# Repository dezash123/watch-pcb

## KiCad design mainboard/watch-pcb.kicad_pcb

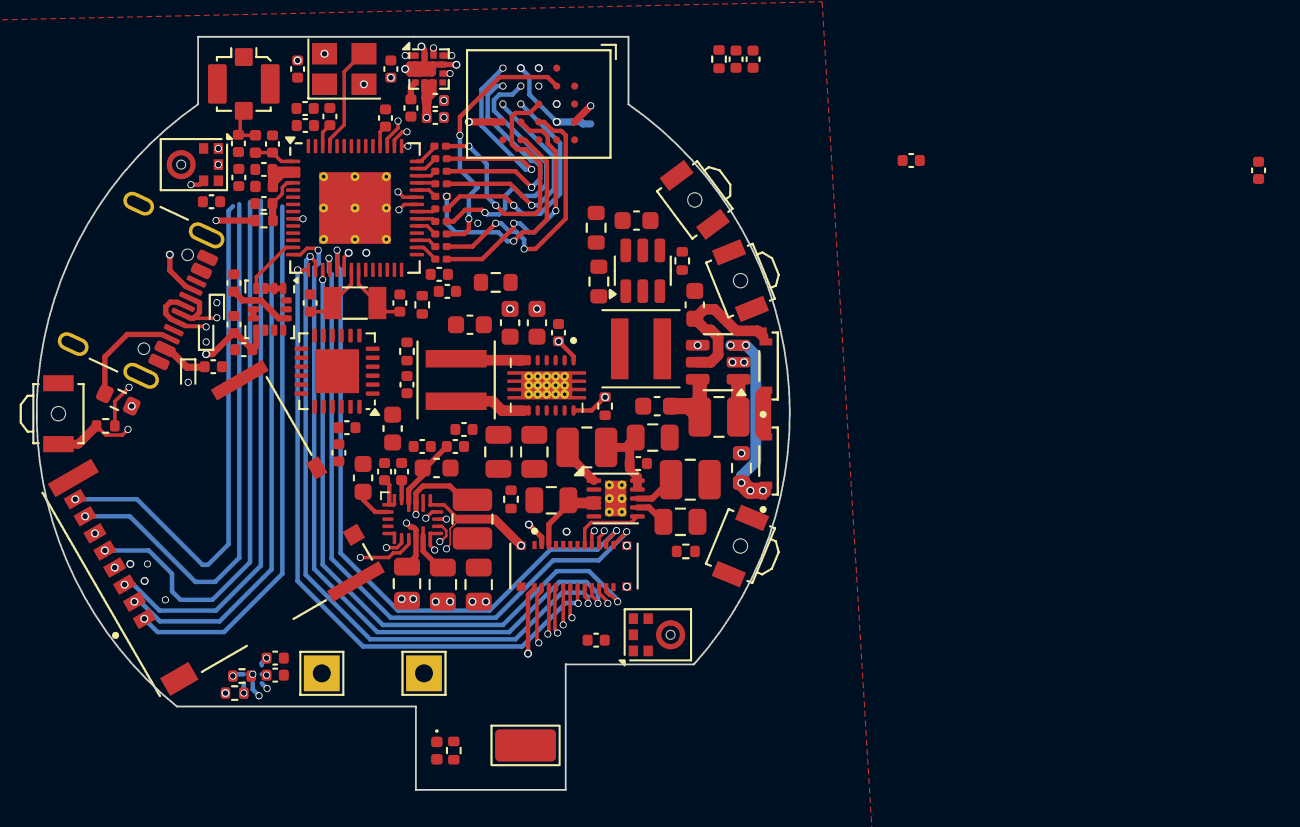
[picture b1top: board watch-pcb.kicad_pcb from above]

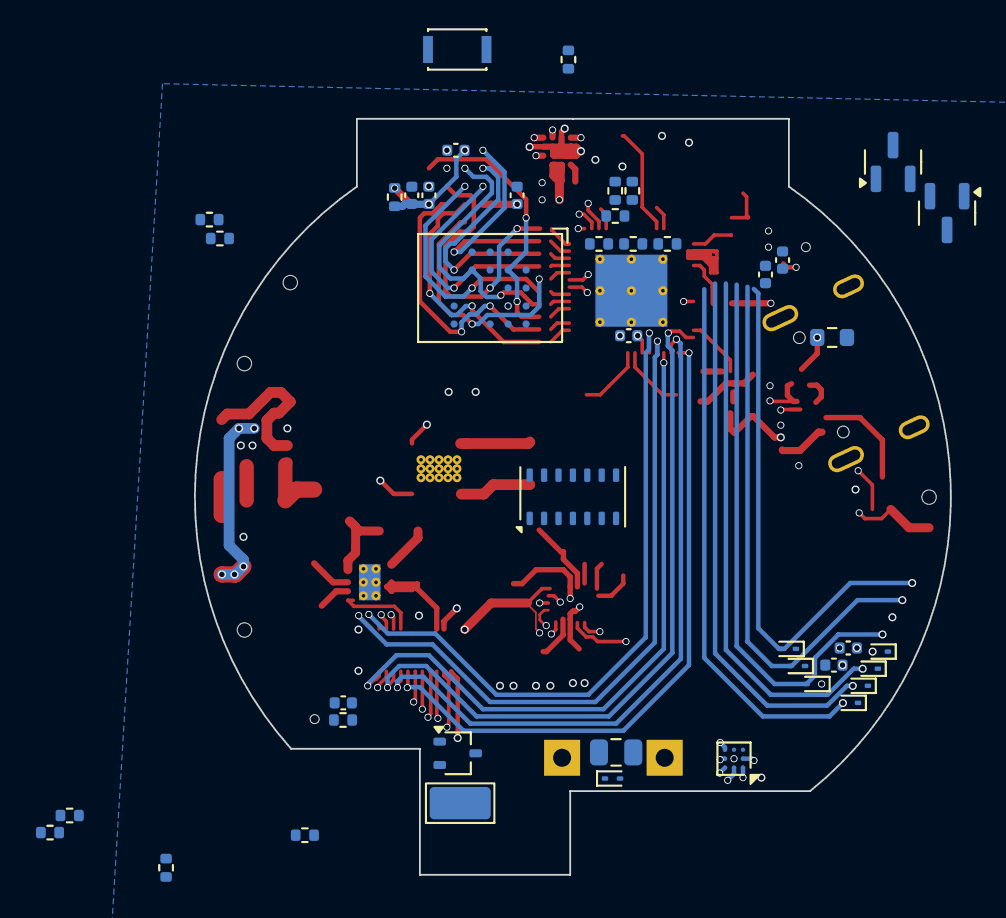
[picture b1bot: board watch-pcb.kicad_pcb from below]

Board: 6 copper layers, 42.0 x 42.0 mm, 166 parts (43 on the bottom side), 111 nets.

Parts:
C1, C4, C9, C17, C19, C23, C27, C41, C44, C48, C70, C72: 1uF; C_0402_1005Metric
C2, C10, C11, C13, C14, C16, C24, C25, C26, C28, C29, C30, C35, C45, C50, C56, C59, C61, C67, C68, C69, C74, C76, C77: 100nF; C_0402_1005Metric
C3: 10uF; C_0603_1608Metric
C5: 47nF; C_0402_1005Metric
C6, C7, C8: 22uF; C_0603_1608Metric
C12, C73, C81: 4.7uF; C_0603_1608Metric
C15, C55, C57, C58, C64, C65, C79, C80: 10uF; C_0805_2012Metric
C18, C33: 10nF; C_0402_1005Metric
C20: 2.2uF; C_0402_1005Metric
C21, C22: 1.5pF; C_0402_1005Metric
C31, C32, C46, C47: C; C_0402_1005Metric
C34, C60: 10uF; C_0402_1005Metric
C51: 1uF; C_0603_1608Metric
C63: 22uF; C_0805_2012Metric
C82: 220nF; C_0603_1608Metric
D1, D2: CUW Y3SH.B2-JD-42-6T; LED_CUW_Y3SH.B2-GFJD-5J6T-Z242-20-R18-Z
D3, D6, D7, D8: ESD9B5.0ST5G; D_SOD-923
D4: CHARGING; LED_0402_1005Metric
D9, D10, D11, D12, D13, D14, D15: ESD9B3.3ST5G; D_SOD-923
J2: USB_C_Receptacle; USB_C_Receptacle_GCT_USB4105-xx-A_16P_TopMnt_Horizontal
J3: ESP_ANT; U.FL_Molex_MCRF_73412-0110_Vertical
J5: Micro_SD_Card; MOLEX_503398-1892
J6: TT143AMC12C; MOLEX_505550-2420
J7: BATT+; TestPoint_THTPad_2.0x2.0mm_Drill1.0mm
J8: BATT-; TestPoint_THTPad_2.0x2.0mm_Drill1.0mm
J9: LASER+; TestPoint_Keystone_5015_Micro_Mini
J10: LASER-; TestPoint_Keystone_5015_Micro_Mini
L1: XFL4020-152ME; L_Coilcraft_XxL4040
L2: CIGT252010EH1R0MNE; L_1008_2520Metric
L3: XFL4020-222ME; L_Coilcraft_XxL4040
L4: 2.7nH; L_0402_1005Metric
L5: LQG15HN2N0C02D; L_0402_1005Metric
L6: 24nH; C_0402_1005Metric
L7, L8: 10uH; L_1008_2520Metric
L9: LQM2HPN4R7MG0L; L_1008_2520Metric
MK1, MK2: ICS-43434; InvenSense_ICS-43434-6_3.5x2.65mm
Q1: BSS214NW; SOT-323_SC-70
Q2, Q3: BSS138; SOT-23
R1, R18, R23, R24, R38, R39, R40, R41, R42, R43: 10k; R_0402_1005Metric
R4: 5; R_0603_1608Metric
R8, R35, R37, R44, R50, R51, R52, R53, R54, R55: 0; R_0201_0603Metric
R9: 5k; R_0402_1005Metric
R10: 1M; R_0402_1005Metric
R11: 5.32k; R_0402_1005Metric
R12: 30.1; R_0402_1005Metric
R13: R; R_0402_1005Metric
R14, R15, R17, R19, R20, R45, R46, R47, R48, R49: 100k; R_0402_1005Metric
R16, R22: 5.1k; R_0603_1608Metric
R26: 0; R_0402_1005Metric
R28: 200k; R_0603_1608Metric
R29: 100k; R_0603_1608Metric
R30: 499k; R_0402_1005Metric
R36: 1k; C_0402_1005Metric
SW1, SW2, SW3, SW4: B3U-3000P-B; SW_SPST_B3U-3000P-B
SW8: BOOT; SW_SPST_CK_KXT3
TH1: 103AT-2 10k; R_0603_1608Metric
U1: TPS63021; Texas_VSON-14_3x4mm_ThermalPad
U2: BQ25628E; Texas_WQFN-18_2.5x3.0mm_P0.4mm
U4: BQ27427YZFR; Texas_DSBGA-9_1.62x1.58mm_Layout3x3_P0.5mm
U5: MX25UM51245GXDI00; BGA-24_6.0x8.0mm_Layout5x5_P1.0mm
U6: S80KS5123GABHV020; BGA-24_6.0x8.0mm_Layout5x5_P1.0mm
U8: TCA9535MRGER; VQFN-24-1EP_4x4mm_P0.5mm_EP2.45x2.45mm
U9: TPS65631W; WSON-10-1EP_2.5x2.5mm_P0.5mm_EP1.2x2mm_ThermalVias
U10: LIS3MDL; LGA-12_2x2mm_P0.5mm
U11: ESP32-S3; QFN-56-1EP_7x7mm_P0.4mm_EP4x4mm_ThermalVias
U12: LSM6DSOXTR; LGA-14_3x2.5mm_P0.5mm_LayoutBorder3x4y
U14: MAX30102; Maxim_OLGA-14_3.3x5.6mm_P0.8mm
U16: AP3019AK; SOT-23-6
U17: TLV62569DDC; SOT-23-6
Y1: 32.768kHz; Crystal_SMD_3215-2Pin_3.2x1.5mm
Y2: 40MHz(10ppm); Crystal_SMD_3225-4Pin_3.2x2.5mm

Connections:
+1V8: C9.1, C10.1, C23.1, C24.2, C25.1, C26.1, C27.1, C28.1, C29.1, C30.1, C72.2, C76.2, L3.2, R19.1, R20.1, R28.1, U5.B4 (VCC), U5.D1 (VCCQ), U5.E4 (VCCQ), U6.B4 (VCC), U6.D1 (VCCQ), U6.E4 (VCCQ), U11.29 (VDD_SPI), U14.11 (VDD)
+3V3: C4.1, C6.2, C7.2, C8.2, C11.1, C13.1, C16.1, C17.1, C33.1, C34.1, C44.2, C45.1, C48.2, C50.2, C55.2, C56.1, C60.2, C61.2, C67.2, C68.2, C69.2, C70.2, C73.1, C74.1, C77.1, D15.2 (A2), J5.4 (VDD), J6.1 (VDD), J6.19 (IOVCC), J6.20 (VDD), J9.1, L5.2, L7.1, MK1.5 (VDD), MK2.2 (LR), MK2.5 (VDD), R10.1, R13.2, R15.2, R17.2, R24.2, R38.1, R39.1, R40.1, R41.1, R42.1, R43.1, R46.1, R47.1, R48.1, R49.1, SW8.1, U1.3 (FB), U1.4 (VOUT), U1.5 (VOUT), U8.21 (VCC), U9.9 (AVIN), U9.10 (PVIN), U10.5 (Vdd), U10.6 (Vdd_IO), U10.10 (~CS), U11.20 (VDD3P3_RTC), U11.46 (VDD3P3_CPU), U11.55 (VDDA), U11.56 (VDDA), U12.5 (VDDIO), U12.8 (VDD), U12.12 (CS), U14.9 (VLED+), U14.10 (VLED+)
+BATT: C15.2, C19.2, C63.1, D3.2 (A2), J7.1, U2.8 (BAT), U4.C3 (BAT)
+VSW: C2.2, C51.1, C64.1, C65.1, C79.1, C80.1, C81.1, L2.2, L9.2, R30.2, U1.1 (VINA), U1.10 (VIN), U1.11 (VIN), U2.9 (SYS), U4.C2 (SRX), U16.6 (V_{IN}), U17.1 (EN), U17.4 (VIN)
/ESP MCU/BOOT: Q2.1 (G), Q3.1 (G), R1.2, SW8.2
/ESP MCU/CLK_N: C47.2, U11.53 (XTAL_N), Y2.3
/ESP MCU/CLK_P: L6.2, U11.54 (XTAL_P)
/ESP MCU/EN: R10.2, R23.1, U1.14 (PG)
/ESP MCU/ESP_ANT: C22.1, L4.2, U11.1 (LNA_IN)
/ESP MCU/EXT_INT: R24.1, U8.22 (~INT), U11.27 (GPIO21)
/ESP MCU/EXT_IO1: J6.5 (RST), U8.1 (P00)
/ESP MCU/EXT_IO2: J6.15 (RST), U8.2 (P01)
/ESP MCU/EXT_IO3: R47.2, SW2.1, U8.3 (P02)
/ESP MCU/EXT_IO4: R48.2, SW3.2, U8.4 (P03)
/ESP MCU/EXT_IO5: R49.2, SW4.1, U8.5 (P04)
/ESP MCU/EXT_IO6: U8.6 (P05), U10.7 (INT)
/ESP MCU/EXT_IO7: R17.1, U4.A1 (GPOUT), U8.7 (P06)
/ESP MCU/EXT_IO8: R15.1, U2.11 (INT), U8.8 (P07)
/ESP MCU/EXT_IO9: R14.1, U1.13 (PS/SYNC), U8.10
/ESP MCU/FSPI_CLK: J6.11 (SCL), U11.17 (GPIO12)
/ESP MCU/FSPI_CS: J6.7 (CS), U11.15 (GPIO10)
/ESP MCU/FSPI_D: J6.8 (D0), U11.16 (GPIO11)
/ESP MCU/FSPI_HD: J6.9 (D3), U11.14 (GPIO9)
/ESP MCU/FSPI_Q: J6.13 (D1), U11.18 (GPIO13)
/ESP MCU/FSPI_WP: J6.14 (D2), U11.19 (GPIO14)
/ESP MCU/I2S_SCK: MK1.4 (SCK), MK2.4 (SCK), U11.45 (MTDO)
/ESP MCU/I2S_SD: MK1.6 (SD), MK2.6 (SD), R45.2, U11.43 (GPIO38)
/ESP MCU/I2S_WS: MK1.1 (WS), MK2.1 (WS), U11.44 (MTCK)
/ESP MCU/IO1: R26.2, U11.9 (GPIO4)
/ESP MCU/IO2: J6.2 (INT), U11.10 (GPIO5)
/ESP MCU/IO3: J6.16 (TE), U11.11 (GPIO6)
/ESP MCU/IO4: R46.2, U11.12 (GPIO7), U14.13 (~INT)
/ESP MCU/IO5: U11.13 (GPIO8), U12.4 (INT1)
/ESP MCU/IO6: R36.1, U11.23 (GPIO17)
/ESP MCU/IO7: U11.24 (GPIO18), U12.9 (INT2)
/ESP MCU/IO8: U10.8 (DRDY), U11.37 (SPICLK_P)
/ESP MCU/IO9: U11.36 (SPICLK_N), U16.4 (CTRL)
/ESP MCU/MCU_SCL: Q3.3 (D), U11.5 (GPIO0)
/ESP MCU/MEM_CLK: R52.2, U5.B2 (SCLK), U6.B2 (CK)
/ESP MCU/MEM_CS0: U5.C2 (CS#), U11.32 (SPICS0)
/ESP MCU/MEM_CS1: U6.A3 (CS#), U11.28 (SPICS1)
/ESP MCU/MEM_D0: R54.2, U5.D3 (SIO0), U6.D3 (DQ0)
/ESP MCU/MEM_D1: R53.2, U5.D2 (SIO1), U6.D2 (DQ1)
/ESP MCU/MEM_D2: R51.2, U5.C4 (SIO2), U6.C4 (DQ2)
/ESP MCU/MEM_D3: R50.2, U5.D4 (SIO3), U6.D4 (DQ3)
/ESP MCU/MEM_D4: R8.2, U5.D5 (SIO4), U6.D5 (DQ4)
/ESP MCU/MEM_D5: R35.2, U5.E3 (SIO5), U6.E3 (DQ5)
/ESP MCU/MEM_D6: R37.2, U5.E2 (SIO6), U6.E2 (DQ6)
/ESP MCU/MEM_D7: R44.2, U5.E1 (SIO7), U6.E1 (DQ7)
/ESP MCU/MEM_DQS: R55.2, U5.C3 (DQS), U6.C3 (RWDS)
/ESP MCU/RTC_N: C32.2, U11.22 (XTAL_32K_N), Y1.1
/ESP MCU/RTC_P: C31.2, U11.21 (XTAL_32K_P), Y1.2
/ESP MCU/SD_CLK: D12.2 (A2), J5.5 (CLK), R41.2, U11.50 (U0RXD)
/ESP MCU/SD_CMD: D11.2 (A2), J5.3 (CMD), R40.2, U11.49 (U0TXD)
/ESP MCU/SD_D0: D13.2 (A2), J5.7 (DAT0), R42.2, U11.51 (GPIO45)
/ESP MCU/SD_D1: D14.2 (A2), J5.8 (DAT1), Q2.3 (D), R43.2, U11.52 (GPIO46)
/ESP MCU/SD_D2: D9.2 (A2), J5.1 (DAT2), R38.2, U11.47 (MTDI)
/ESP MCU/SD_D3: D10.2 (A2), J5.2 (DAT3/CD), R39.2, U11.48 (MTMS)
/ESP MCU/USB_D+: D7.2 (A2), J2.A6 (D+), J2.B6 (D+), U11.26 (GPIO20/USB_D+)
/ESP MCU/USB_D-: D8.2 (A2), J2.A7 (D-), J2.B7 (D-), U11.25 (GPIO19/USB_D-)
/IO/AMOLED_M: C58.2, J6.23 (ELVSS), U9.7 (OUTN)
/IO/AMOLED_P: C57.2, J6.22 (ELVDD), U9.3 (OUTP), U9.4 (FBS)
/IO/SWIRE: J6.17 (SWIRE), U9.6 (CTRL)
/USB and Power/1V8G: R30.1, U1.12 (EN), U17.5 (PG)
/USB and Power/SCL: U2.13 (SCL), U4.A3 (SCL)
/USB and Power/SDA: U2.12 (SDA), U4.A2 (SDA)
GND: C1.2, C2.1, C3.1, C4.2, C6.1, C7.1, C8.1, C9.2, C10.2, C11.2, C12.2, C13.2, C14.2, C15.1, C16.2, C17.2, C18.2, C19.1, C20.1, C21.2, C22.2, C23.2, C24.1, C25.2, C26.2, C27.2, C28.2, C29.2, C30.2, C31.1, C32.1, C33.2, C34.2, C35.2, C41.2, C44.1, C45.2, C46.2, C47.1, C48.1, C50.1, C51.2, C55.1, C56.2, C57.1, C58.1, C59.1, C60.1, C61.1, C63.2, C64.2, C65.2, C67.1, C68.1, C69.1, C70.1, C72.1, C73.2, C74.2, C76.1, C77.2, C79.2, C80.2, C81.2, C82.2, D3.1 (A1), D6.2 (A2), D7.1 (A1), D8.1 (A1), D9.1 (A1), D10.1 (A1), D11.1 (A1), D12.1 (A1), D13.1 (A1), D14.1 (A1), D15.1 (A1), J2.A1 (GND), J2.A12 (GND), J2.B1 (GND), J2.B12 (GND), J2.S1 (SHIELD), J3.2 (Ext), J5.6 (VSS), J5.9 (SHIELD), J6.6 (GND), J6.10 (GND), J6.12 (GND), J6.18 (GND), J6.24 (MTP_PWR), J6.SH (SHIELD), J8.1, L8.1, MK1.2 (LR), MK1.3 (GND), MK2.3 (GND), Q1.2 (S), Q2.2 (S), Q3.2 (S), R1.1, R4.2, R9.2, R12.1, R14.2, R16.2, R18.1, R22.2, R29.2, R45.1, SW1.2, SW2.2, SW3.1, SW4.2, TH1.1, U1.2 (GND), U1.15 (PGND), U2.14 (CE), U2.15 (GND), U4.B2 (VSS), U4.C1 (VSS), U5.B3 (GND), U5.C1 (VSSQ), U5.E5 (VSSQ), U6.B1 (CK#), U6.B3 (VSS), U6.C1 (VSSQ), U6.E5 (VSSQ), U8.9 (GND), U8.18 (A0), U8.23 (A1), U8.24 (A2), U8.25 (EPAD), U9.2 (PGND), U9.5 (AGND), U9.11 (GND), U10.2 (GND), U10.3 (GND), U10.9 (SDO/SA1), U10.12 (GND), U11.57 (GND), U12.1 (SDO/SA0), U12.2 (SDX), U12.3 (SCX), U12.6 (GND), U12.7 (GND__1), U14.4 (PGND), U14.12 (GND), U16.2 (GND), U17.2 (GND), Y2.2, Y2.4
unnamed: C14.1, L5.1, U11.2 (VDD3P3), U11.3 (VDD3P3)
unnamed: C46.1, L6.1, Y2.1
unnamed: C82.1, D1.2 (A), U16.5 (V_{OUT})
unnamed: D1.1 (K), D2.2 (A)
unnamed: D2.1 (K), R4.1, U16.3 (FB)
unnamed: D4.2 (A), R13.1
unnamed: D4.1 (K), U2.10 (STAT)
unnamed: J2.A5 (CC1), R16.1
unnamed: J2.B5 (CC2), R22.1
unnamed: C21.1, J3.1 (In), L4.1
unnamed: J10.1, Q1.3 (D)
unnamed: L1.1, U1.8 (L1), U1.9 (L1)
unnamed: L1.2, U1.6 (L2), U1.7 (L2)
unnamed: Q1.1 (G), R36.2
unnamed: C5.1, U2.1 (BTST)
unnamed: R9.1, U2.4 (ILIM)
unnamed: C3.2, C35.1, U2.17 (PMID)
unnamed: R26.1, SW1.1, U2.7 (QON)
unnamed: C12.1, U2.2 (REGN)
unnamed: C5.2, L2.1, U2.16 (SW)
unnamed: R11.1, R12.2, TH1.2, U2.6 (TS)
unnamed: R11.2, U2.5 (TS_BIAS)
unnamed: R18.2, U4.B1 (BIN)
unnamed: C20.2, U4.B3 (VDD)
unnamed: R20.2, U5.A4 (RESET#)
unnamed: R19.2, U6.A4 (RST#)
unnamed: L8.2, U9.8 (SWN)
unnamed: L7.2, U9.1 (SWP)
unnamed: C59.2, U10.4 (C1)
unnamed: C41.1, R23.2, U11.4 (CHIP_PU)
unnamed: R8.1, U11.38 (GPIO33)
unnamed: R35.1, U11.39 (GPIO34)
unnamed: R37.1, U11.40 (GPIO35)
unnamed: R44.1, U11.41 (GPIO36)
unnamed: R55.1, U11.42 (GPIO37)
unnamed: R52.1, U11.33 (SPICLK)
unnamed: R54.1, U11.35 (SPID)
unnamed: R50.1, U11.30 (SPIHD)
unnamed: R53.1, U11.34 (SPIQ)
unnamed: R51.1, U11.31 (SPIWP)
unnamed: L9.1, U16.1 (SW)
unnamed: R28.2, R29.1, U17.6 (FB)
unnamed: L3.1, U17.3 (SW)
VBUS: C1.1, C18.1, D6.1 (A1), J2.A4 (VBUS), J2.A9 (VBUS), J2.B4 (VBUS), J2.B9 (VBUS), U2.18 (VBUS)

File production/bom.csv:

Designator,Footprint,Quantity,Value,LCSC Part #
"C21, C22",0402,2,1.5pF,
"C27, C34, C36, C39, C41, C48, C51, C72, C75, C78",0402,10,1uF,
"C28, C29, C30, C35, C37, C38, C42, C43, C50, C54, C56, C59, C62, C67, C68, C71, C76, C77",0402,18,100nF,
"C31, C32, C46, C47",0402,4,C,
C33,0402,1,10nF,
"C40, C55, C57, C58",0402,4,10uF,
C63,0805,1,22uF,
"C73, C81",0603,2,4.7uF,
C82,0603,1,220nF,
C84,0603,1,10uF,
"D1, D2",LED_CUW_Y3SH.B2-GFJD-5J6T-Z242-20-R18-Z,2,CUW Y3SH.B2-JD-42-6T,
D3,D_SOD-923,1,ESD9B5.0ST5G,
J10,TestPoint_Keystone_5015_Micro_Mini,1,LASER-,
J11,TestPoint_THTPad_1.5x1.5mm_Drill0.7mm,1,MTR+,
J13,TestPoint_THTPad_1.5x1.5mm_Drill0.7mm,1,MTR-,
J2,USB_C_Receptacle_GCT_USB4105-xx-A_16P_TopMnt_Horizontal,1,USB_C_Receptacle,
J3,U.FL_Molex_MCRF_73412-0110_Vertical,1,ESP_ANT,
J5,MOLEX_503398-1892,1,Micro_SD_Card,
J6,MOLEX_505550-2420,1,TT143AMC12C,
J7,TestPoint_THTPad_2.0x2.0mm_Drill1.0mm,1,BATT+,
J8,TestPoint_THTPad_2.0x2.0mm_Drill1.0mm,1,BATT-,
J9,TestPoint_Keystone_5015_Micro_Mini,1,LASER+,
L3,L_Coilcraft_XxL4040,1,XFL4020-222ME,
L4,0402,1,2.7nH,
L5,0402,1,2nH,
L6,0402,1,24nH,
"L7, L8",1008,2,10uH,
L9,1008,1,LQM2HPN4R7MG0L,
"MK1, MK2",InvenSense_ICS-43434-6_3.5x2.65mm,2,ICS-43434,
Q1,SOT-323_SC-70,1,BSS214NW,
R16,0603,1,5.1k,
R23,0402,1,10k,
R26,0402,1,0,
R28,0603,1,200k,
R29,0603,1,100k,
R30,0402,1,499k,
"R35, R37, R44, R50, R51, R52, R53, R54, R55, R8",0201,10,0,
R36,0402,1,1k,
R4,0603,1,5,
"R45, R46, R47, R48, R49",0402,5,100k,
SW1,SW_SPST_B3U-3000P,1,B3U-3000P,
"SW3, SW4, SW5",SW_SPST_B3U-3000P,3,SW_Push,
SW8,SW_SPST_CK_KXT3,1,BOOT,
U10,LGA-12_2x2mm_P0.5mm,1,LIS3MDL,
U13,VSSOP-10_3x3mm_P0.5mm,1,DRV2605LDGS,
U14,Maxim_OLGA-14_3.3x5.6mm_P0.8mm,1,MAX30102,
U16,SOT-23-6,1,AP3019AK,
U17,SOT-23-6,1,TLV62569DDC,
U3,Bosch_LGA-8_2.5x2.5mm_P0.65mm_ClockwisePinNumbering,1,BME280,
U5,BGA-24_6.0x8.0mm_Layout5x5_P1.0mm,1,MX25UM51245GXDI00,
U6,BGA-24_6.0x8.0mm_Layout5x5_P1.0mm,1,S80KS5123GABHV020,
U7,QFN-56-1EP_7x7mm_P0.4mm_EP4x4mm_ThermalVias,1,ESP32-S3,
U9,WSON-10-1EP_2.5x2.5mm_P0.5mm_EP1.2x2mm_ThermalVias,1,TPS65631W,
Y1,Crystal_SMD_3215-2Pin_3.2x1.5mm,1,32.768kHz,
Y2,Crystal_SMD_3225-4Pin_3.2x2.5mm,1,40MHz(10ppm),

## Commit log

2025-03-08 adding existing progress/reorganization
2025-03-10 done with stm, going back to esp
2025-03-12 quicksaving pcb bc im gonna redo it
2025-03-13 no more daughter probably
2025-03-23 basically done with board layout, gonna try to do a smaller one (47->42mm diameter)
2025-05-15 layout done probably
2025-06-29 finally routed the memory :D
2025-09-04 old changes
2025-09-04 clean heavily
2025-09-04 remove backups from git
2025-09-04 clean more
2025-09-04 remove all features idrc abt from schematic
2025-09-04 mostly cleaned pcb after removals
2025-09-04 more updates
